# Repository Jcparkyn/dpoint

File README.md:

# D-POINT: Digital Pen with Optical-Inertial Tracking

**D-POINT** is an open-source digital stylus that uses camera tracking and inertial measurements to achieve 6DoF (six degrees of freedom) inputs, with low latency, pressure sensitivity, and sub-millimetre accuracy.
The stylus can be used on any flat surface, and works with consumer-grade webcams.

<video src="https://github.com/Jcparkyn/dpoint/assets/51850908/21d00ce3-6456-4fba-8c24-4bc8e6642a0d" width="1920" height="1080" autoplay loop muted></video>

This project was part of my undergraduate thesis for electrical engineering. I've open-sourced the code and design files in the hopes that they might be useful to somebody, but it's not intended to be a "plug and play" DIY project. If you want to try building it anyway, follow the [setup guide](./setup-guide.md).

## Design

This is a very brief overview of how the system works. For all the details, plus literature review and lots of evaluation, read the full thesis (note: I haven't published this online yet).

### Hardware

The main body of the stylus was 3D printed as two halves, shown below. The stylus contains a force sensor, a Li-ion battery which charges over USB-C, and an Arduino-based development board for logic and Bluetooth. Eight printed [ArUco](https://www.uco.es/investiga/grupos/ava/portfolio/aruco/) markers are glued to the back of the stylus, for visual pose estimation.

### Visual pose estimation (VPE)

The VPE process involves the four main steps:
1. **Marker detection:** First, we use OpenCV to detect the corners of each visible ArUco marker on the stylus.
1. **Rolling shutter correction:** We use a simple 2D motion model to estimate and correct for the effects of [rolling shutter](https://en.wikipedia.org/wiki/Rolling_shutter) on the observed corner locations.
1. **Perspective-n-Point (PnP):** From these corner positions, we use a [PnP](https://en.wikipedia.org/wiki/Perspective-n-Point) algorithm to estimate the pose of the stylus relative to the camera. When possible, we use the pose from the previous frame as a starting point to refine with virtual visual servoing (VVS), otherwise we fall back to SQPnP.
1. **Coordinate conversion:** Using the calibrated pose of the stylus and the drawing surface relative to the camera, we calculate the position and orientation of the stylus tip relative to the drawing surface.

### Inertial fusion

We use an Extended Kalman Filter (EKF) to fuse the VPE estimates with the inertial data from the accelerometer and gyroscope, and refine the estimates in real-time using the Rauch-Tung-Striebel (RTS) algorithm. To account for time delay from the camera frames, we use a negative-time measurement update algorithm. The EKF is implemented using NumPy and [Numba](https://numba.pydata.org/).

Using inertial measurements allows us to dramatically reduce latency compared to a camera-only implementation, while also improving accuracy and report rate for fast movements.

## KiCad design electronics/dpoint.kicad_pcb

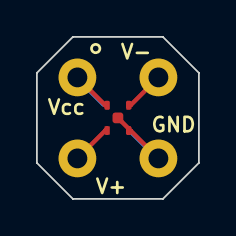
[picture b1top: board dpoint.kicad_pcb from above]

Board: 2 copper layers, 9.0 x 9.0 mm, 6 parts (1 on the bottom side), 4 nets.

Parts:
C1: 0.1u; C_0805_2012Metric_Pad1.18x1.45mm_HandSolder
J1, J2, J3, J4: Conn_01x01_Socket; SolderWire-0.5sqmm_1x01_D0.9mm_OD2.1mm
U1: HSFPAR003A; Alps_HSFPAR003A

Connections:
unnamed: C1.1, J4.1, U1.1 (Vdd)
unnamed: J1.1, U1.4 (V1)
unnamed: J2.1, U1.2 (V2)
unnamed: C1.2, J3.1, U1.3 (GND)

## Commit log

2023-05-13 Add python project
2023-05-13 Add matlab project
2023-05-20 Format python code
2023-06-19 Update parameter values for 120Hz
2023-06-19 Change default camera position
2023-06-19 Add arduino code to repo
2023-06-19 Implement automatic disconnect when stylus not moving
2023-06-27 Increase IMU sample rate and tweak constants
2023-06-28 Add improved camera calibration using a charuco board
2023-06-28 Use charuco board for camera pose estimation
2023-06-28 Replace box visualisation with custom mesh
2023-07-03 Use BLE for transmitting IMU data
2023-07-03 Update marker positions
2023-07-06 Rewrite EKF in python
2023-07-07 Increase stayAwakeThreshold
2023-07-07 Improve PnP algorithm to switch between refinement and EPnP
2023-07-07 Move default camera to focus on middle of charuco board
2023-07-07 Improve quaterion handling to avoid discontinuities
2023-07-07 Update tracking parameters
2023-07-08 Improve coordinate conversion logic
2023-07-08 Fix BLE disconnect callback
2023-07-08 Convert EKF to z-up coordinate system
2023-07-08 Switch to contour corner refinement
2023-07-09 Improve reprojection error check and lower threshold
2023-07-09 Switch to VVS pose refinement, which appears to diverge less often than LM
2023-07-10 Add tip marker to tracker window again
2023-07-10 Fix initial calibration handling
2023-07-10 New stylus dimensions
2023-07-10 Improve reprojectionError metric using RMS instead of mean
2023-07-11 Implement EKF smoothing
2023-07-11 Update test snapshot
2023-07-11 MCU improvements
    - Better BLE handling
    - RGB status LED
    - Sleep when BLE idle
2023-07-11 Separate core tracking logic to MarkerTracker class
2023-07-11 Update process values for sensor bias
2023-07-12 Update marker positions again
2023-07-12 Implement forward-prediction from IMU data
2023-07-16 Broken implementation of marker calibration
2023-07-16 Use numba to JIT compile EKF code
2023-07-16 Move jitted functions to separate file
2023-07-16 JIT remaining ekf functions
2023-07-16 Update filter params
2023-07-16 Improve filter reset logic
2023-07-23 Implement firmware and software for pressure sensitivity
2023-07-31 Update pressure values for new nib
2023-07-31 Remove unneeded print
2023-08-02 Improve naming in app.py
2023-08-02 Implement graceful BLE disconnect
2023-08-02 Use NamedTuple for camera readings
2023-08-02 Upgrade to python 3.11
2023-08-15 Make line black by default
2023-08-15 Improve data type for marker tracker
2023-08-15 Basic implementation of offline playback
2023-08-15 Add code for computing camera covariance matrix
2023-08-16 Slightly improve marker locations
2023-08-16 Implement better recording and playback
2023-08-16 Add recorded data
2023-08-20 Replace offline vispy plot with seaborn for thesis
2023-08-20 Switch to 2D agg line for better rendering quality
2023-08-28 Implement marker calibration and minor refactoring
2023-08-28 Add basic rolling shutter compensation
2023-08-28 Fix rare discontinuity in quaternion state
2023-08-28 Clean up filter code
2023-08-28 Add option to switch to 3D line
2023-08-29 Fix mutation of rvec and tvec from solvePnPRefineVVS
2023-08-29 Formatting
2023-08-29 Adjust state resetting threshold
2023-08-30 Fix typo in idealMarkerPositions
2023-08-30 Add tip position readout to marker_tracker
2023-08-30 Update stylus length dimension
2023-09-02 Add error values to offline plot
2023-09-02 Implement basic auto-focus
2023-09-02 Add code for tip position accuracy plots
2023-09-05 Add more tip position analysis
2023-09-05 Set bandwidths for IMU
2023-09-05 Add retry logic to BLE process
2023-09-06 Refactor load_marker_positions
2023-09-06 Refactor handling of smoothing_length in filter
2023-09-06 Implement raw frame recording
2023-09-06 Improve offline playback, move plotting code to notebook
2023-09-06 Cleanup offline_playback
2023-09-06 Add smoothing length comparison plot
2023-09-10 Blend new data smoothly to avoid jumps
2023-09-10 Add FPS comparison plots
2023-09-10 Add cameraonly plot
2023-09-10 Clean up static tip pos analysis
2023-09-12 Fix bounds for cameronly playback
2023-09-12 Make fps plot use period for x axis
2023-09-17 Use more compact BLE data
2023-09-17 Replace dict with custom types
2023-09-17 Reduce BLE connection interval, and read pressure first
2023-09-17 Increase rate to 130Hz
2023-09-17 Adjust filter params
2023-09-17 Reduce camera exposure
2023-09-17 Fix incompatibility with recorded StylusReading values
2023-09-17 Update plots
2023-09-17 Convert calibratedMarkerPositions to JSON
2023-09-17 Move camera params file
2023-09-17 Move pen OBJ
2023-09-17 Reorganise python project
2023-09-18 Convert recorded readings to JSON
2023-09-18 Commit important recording data to repo
2023-09-18 Move some things to analysis dir
2023-09-18 Move latency measurements to analysis dir
2023-09-18 Fix variable name regression
2023-09-18 Update gitignore
2023-09-18 Implement marker search space refinement
2023-09-19 Improve marker search space algorithm
2023-09-19 Add timing statistics to offline_ope
2023-09-19 Don't crash if camera calibration fails
2023-09-19 Add timing info to offline_playback
2023-09-20 Add debug check
2023-09-22 Improve colors
2023-09-24 TEXT_COL variable
2023-09-24 Convert most camelCase to snake_case
2023-10-01 Set battery charge rate to 100mA
2023-10-01 Plot changes
2023-10-06 Add comment for AIN error
2023-10-06 Replace MCU code with non-mbed implementation
2023-10-09 Remove old matlab files from repo
2023-10-09 Add KiCad files
2023-10-09 Add 3D print files
2023-10-09 Add marker files
2023-10-09 Add readme
2023-10-09 Add license
2023-10-09 Add diagram to readme
2023-10-09 Remove ipynb noise from linguist stats
2023-10-10 Clean up MCU code
2023-10-10 Improve line rendering
2023-10-10 Add basic gui widgets to app
2023-10-10 Skip rendering points where both ends have zero pressure
2023-10-11 Improve tap interrupt parameters
2023-10-11 Add undo and separate colours to app
2023-10-18 Add video to readme
2023-11-08 Use default position for tracker window
2023-11-08 Add latency boxplot
2023-11-08 Switch to DICT_4X4 aruco board
2023-11-08 App improvements
    - Refresh canvas after clearing lines
    - Attempt do disable vsync (usually gets overriden by GPU setting)
    - Make axes smaller
2023-11-08 Move offline_playback to analysis dir, upgrade seaborn
2023-11-11 Add PDF version of stylus-markers
2023-11-11 Update board details for calibrate_camera
2023-11-11 Add setup guide
2023-11-11 Add images to setup guide
2023-11-11 Fix typo in filename
2023-11-20 Add more detail to setup guide
    - platform info
    - configuration and tuning
    - missing sentence about LEDs
2023-11-20 Add docstrings for top-level scripts
2023-11-20 Fix typo
2023-11-20 Simplify main requirements.txt file, move analysis deps to separate file
2023-11-27 Fix type hint
2023-11-27 Fix charuco board for camera calibration
